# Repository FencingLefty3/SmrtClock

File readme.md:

# SMRTClock Hardware Project

This is a project for Stardance blair! I made it with, KiCAD, and AutoCAD. 

## Images

## Bill of Meterials

1         Rotary dial cap.

2         Keycaps of Choosing

1	        Buzzer

1	        Conn_01x08_Pin

2	        SW_Push

1	        RotaryEncoder_Switch

1	        XIAO-ESP32-C3-SMD

1         Case part(s) 3D Print

1x       2.54mm 8 Pin Male Header (For connecting your screen)
      
8x       20cm Female-Female Jumper Wires (For connecting your screen off of the pcb)

8x      M3x5x4 Heatset Inserts

4x     M3x8mm Screws

4x    M3x16mm Screws

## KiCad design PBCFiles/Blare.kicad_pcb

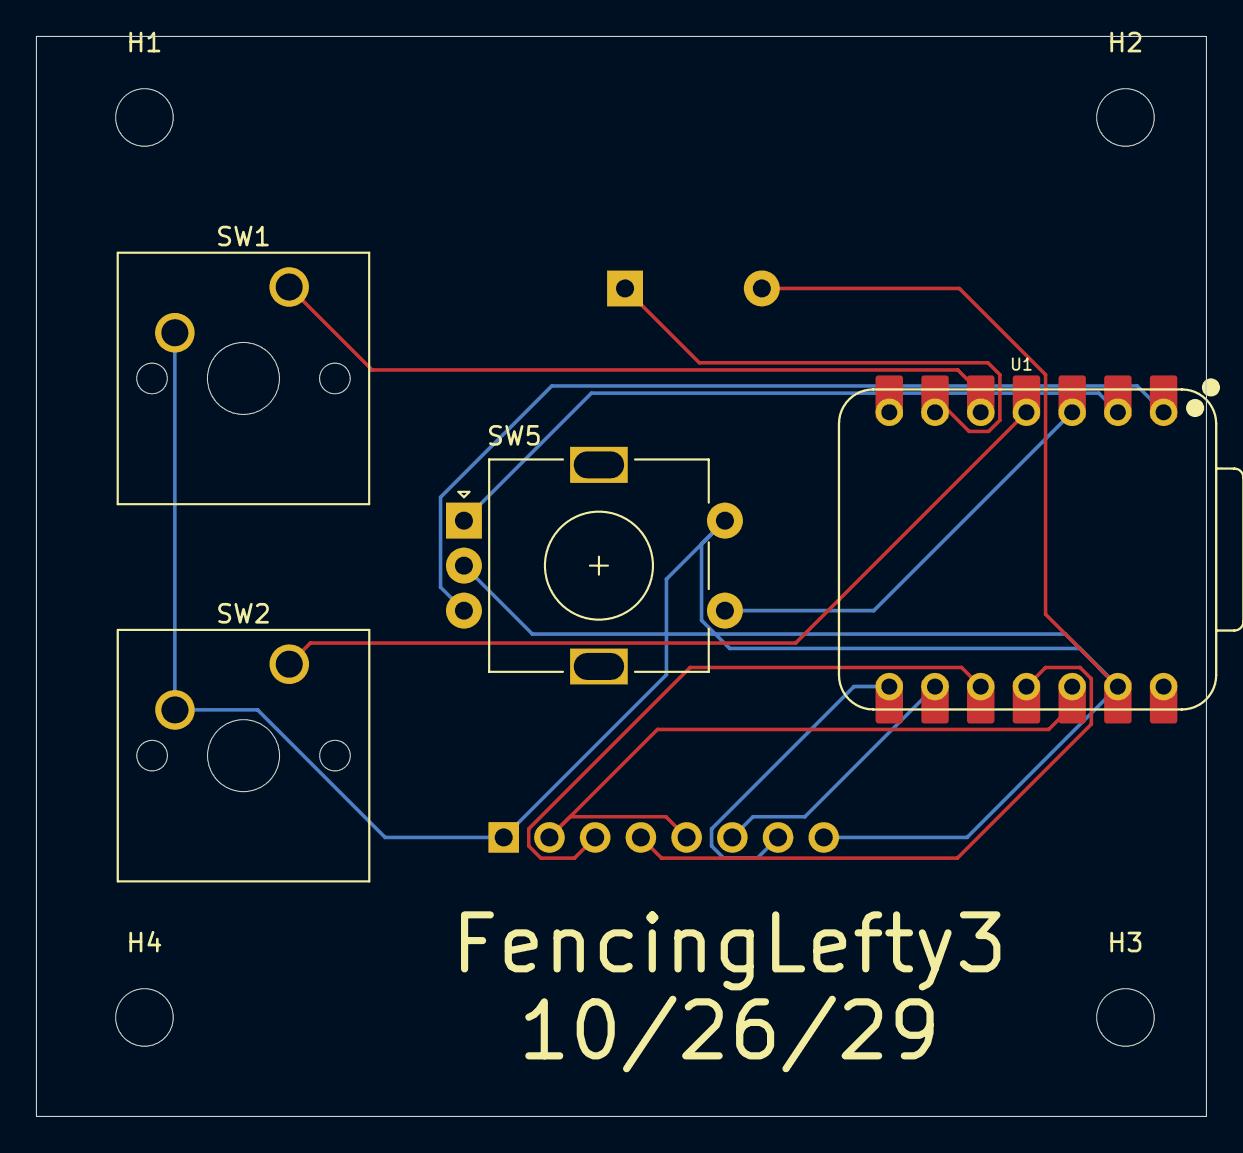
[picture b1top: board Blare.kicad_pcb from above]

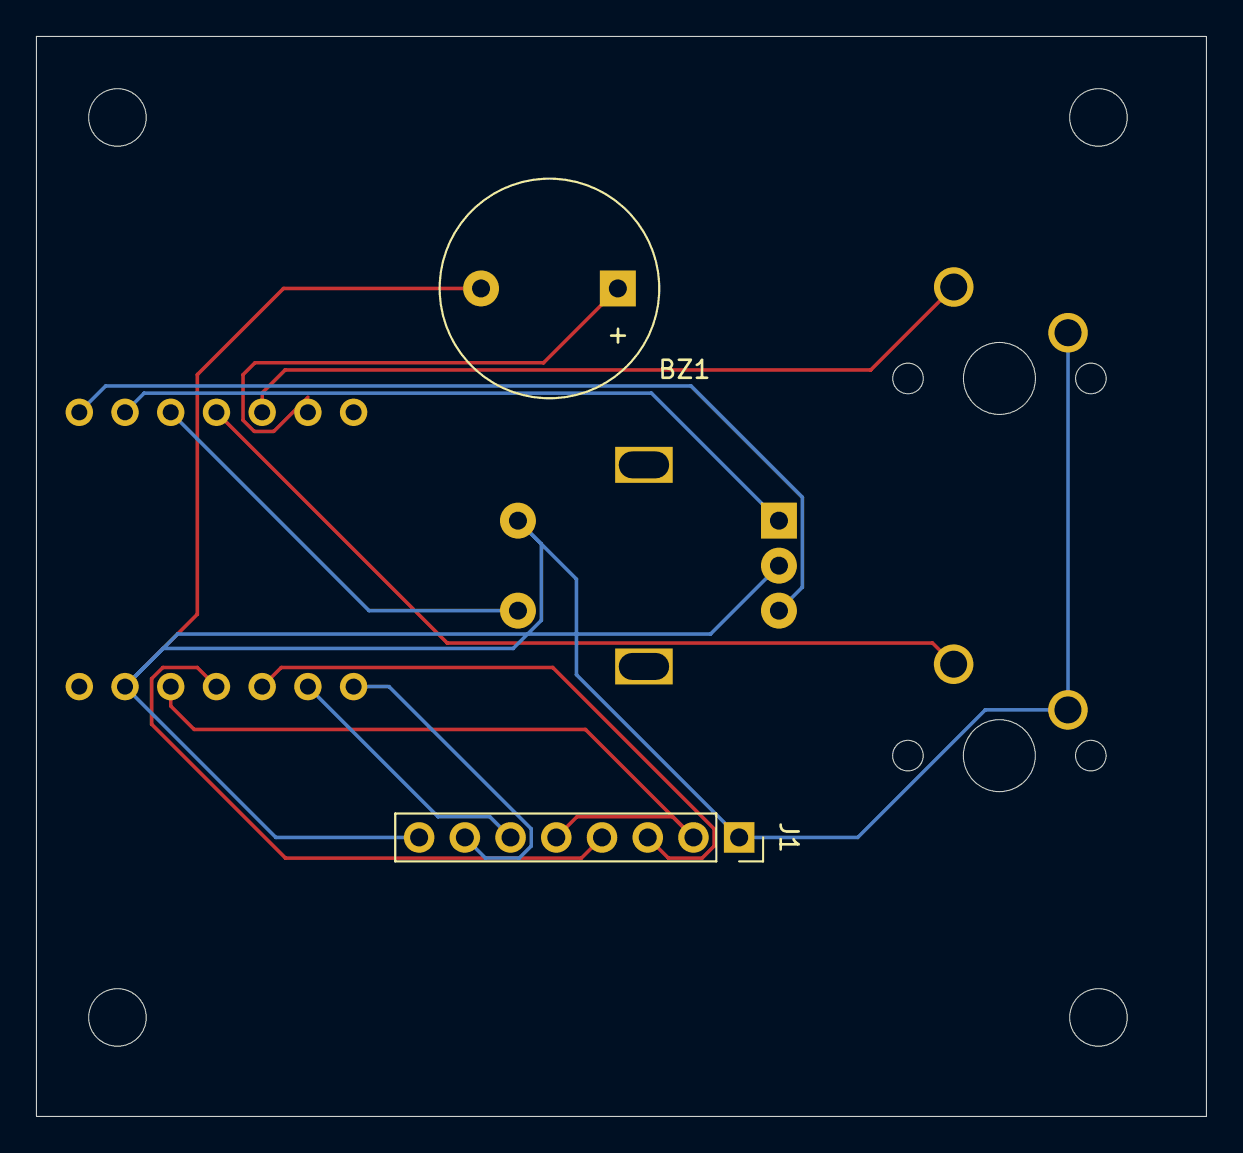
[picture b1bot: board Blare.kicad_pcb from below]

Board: 2 copper layers, 65.0 x 60.0 mm, 10 parts (2 on the bottom side), 12 nets.

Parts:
BZ1: Buzzer; Buzzer_12x9.5RM7.6
H1, H2, H3, H4: MountingHole; MountingHole_3.2mm_M3
J1: Conn_01x08_Pin; PinSocket_1x08_P2.54mm_Vertical
SW1, SW2: SW_Push; SW_Cherry_MX_1.00u_PCB
SW5: RotaryEncoder_Switch; RotaryEncoder_Alps_EC11E-Switch_Vertical_H20mm
U1: XIAO-ESP32-C3-SMD; XIAO-ESP32-C3-DIP

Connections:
+3.3V: J1.2, J1.5, U1.12 (3V3_OUT)
/CS: J1.7, U1.8 (D7)
/DC: J1.6, U1.9 (D8)
/SCL: J1.3, U1.10 (D9/BOOT)
/SDA: J1.4, U1.11 (D10)
GND: BZ1.2 (-), J1.1, J1.8, SW1.2, SW2.2, SW5.C, SW5.S2, U1.13 (GND)
unnamed: BZ1.1 (+), U1.6 (D5)
unnamed: SW5.B, U1.1 (D0)
unnamed: SW5.A, U1.2 (D1)
unnamed: SW5.S1, U1.3 (D2)
unnamed: SW2.1, U1.4 (D3)
unnamed: SW1.1, U1.5 (D4)
